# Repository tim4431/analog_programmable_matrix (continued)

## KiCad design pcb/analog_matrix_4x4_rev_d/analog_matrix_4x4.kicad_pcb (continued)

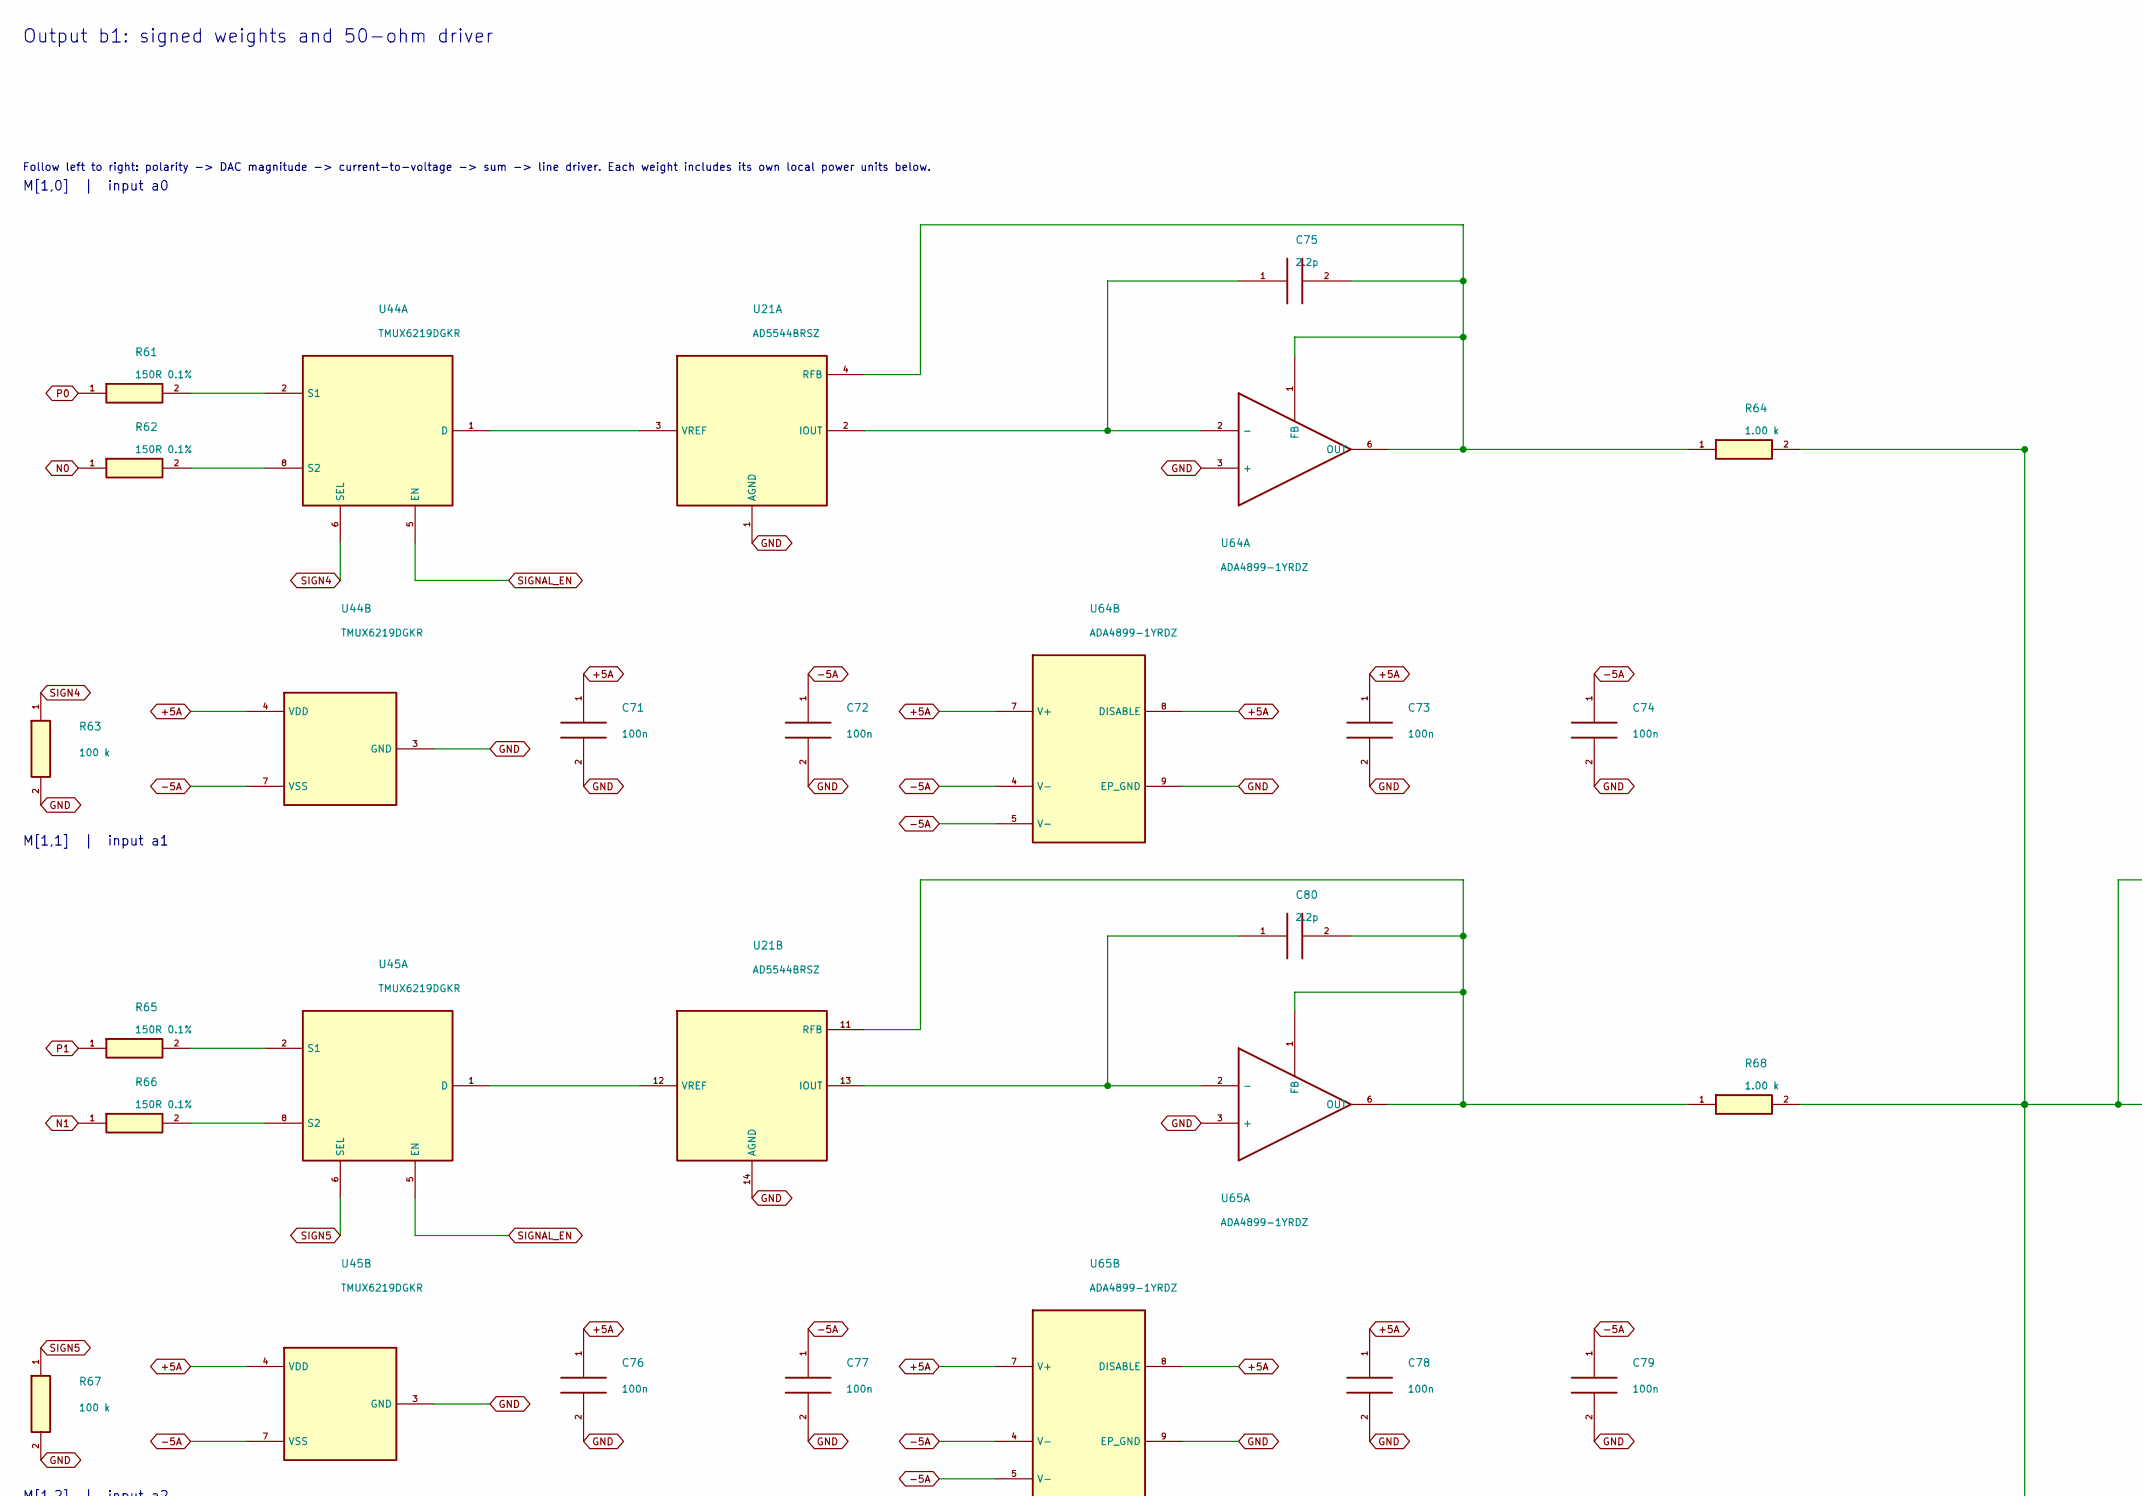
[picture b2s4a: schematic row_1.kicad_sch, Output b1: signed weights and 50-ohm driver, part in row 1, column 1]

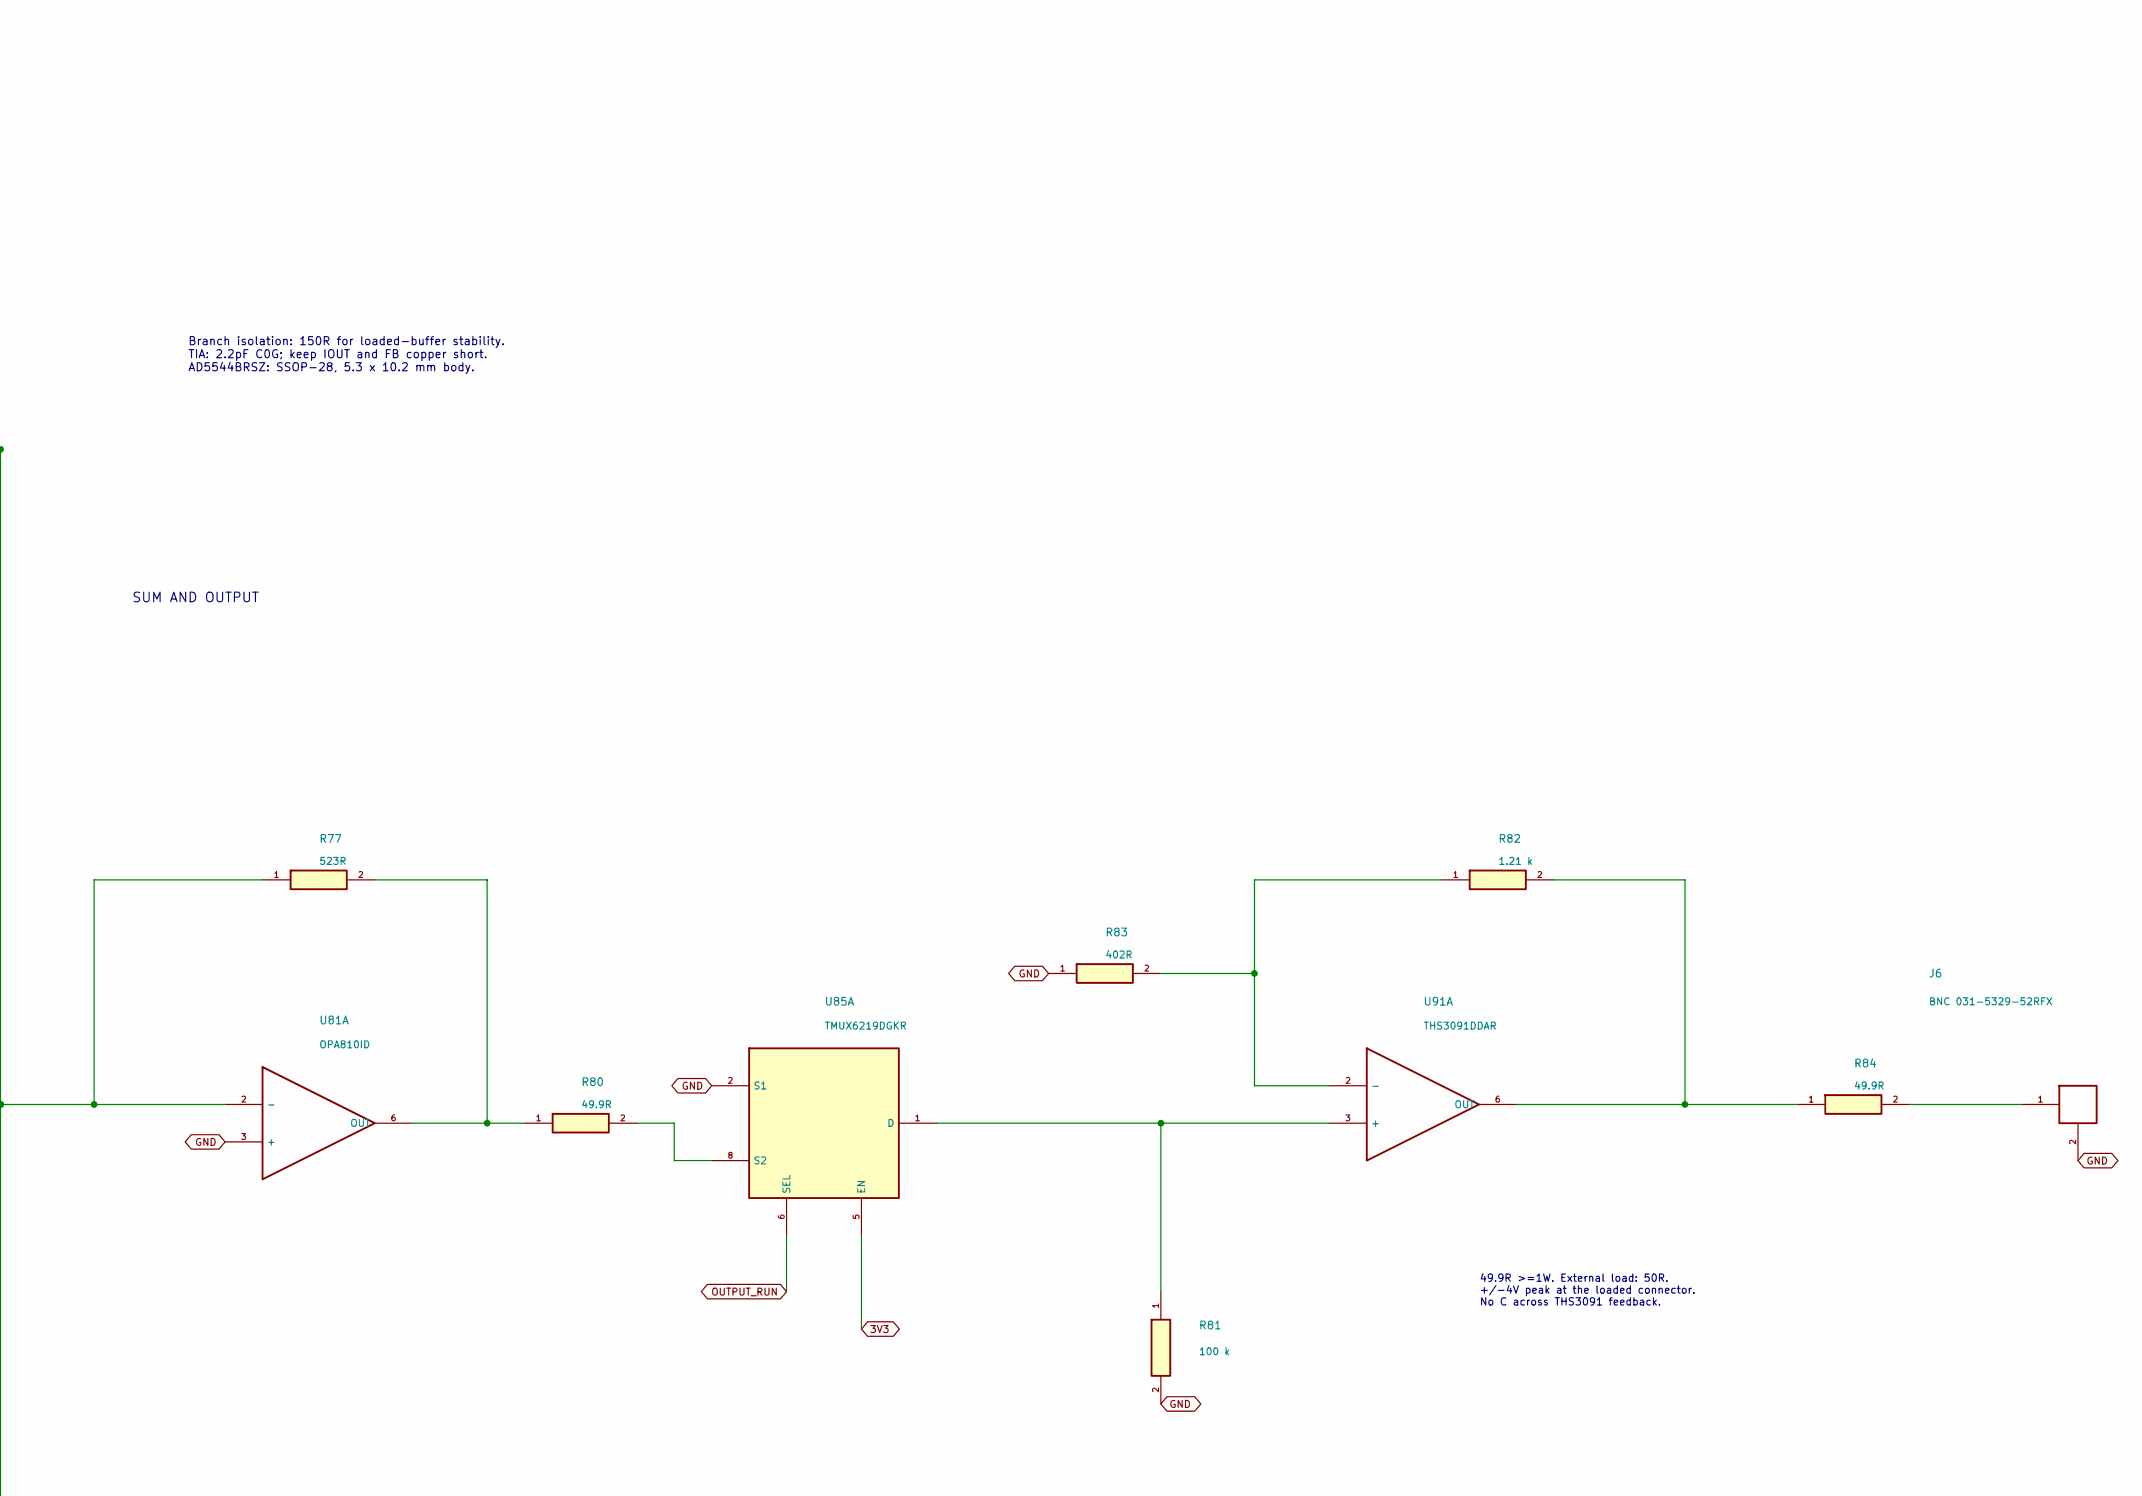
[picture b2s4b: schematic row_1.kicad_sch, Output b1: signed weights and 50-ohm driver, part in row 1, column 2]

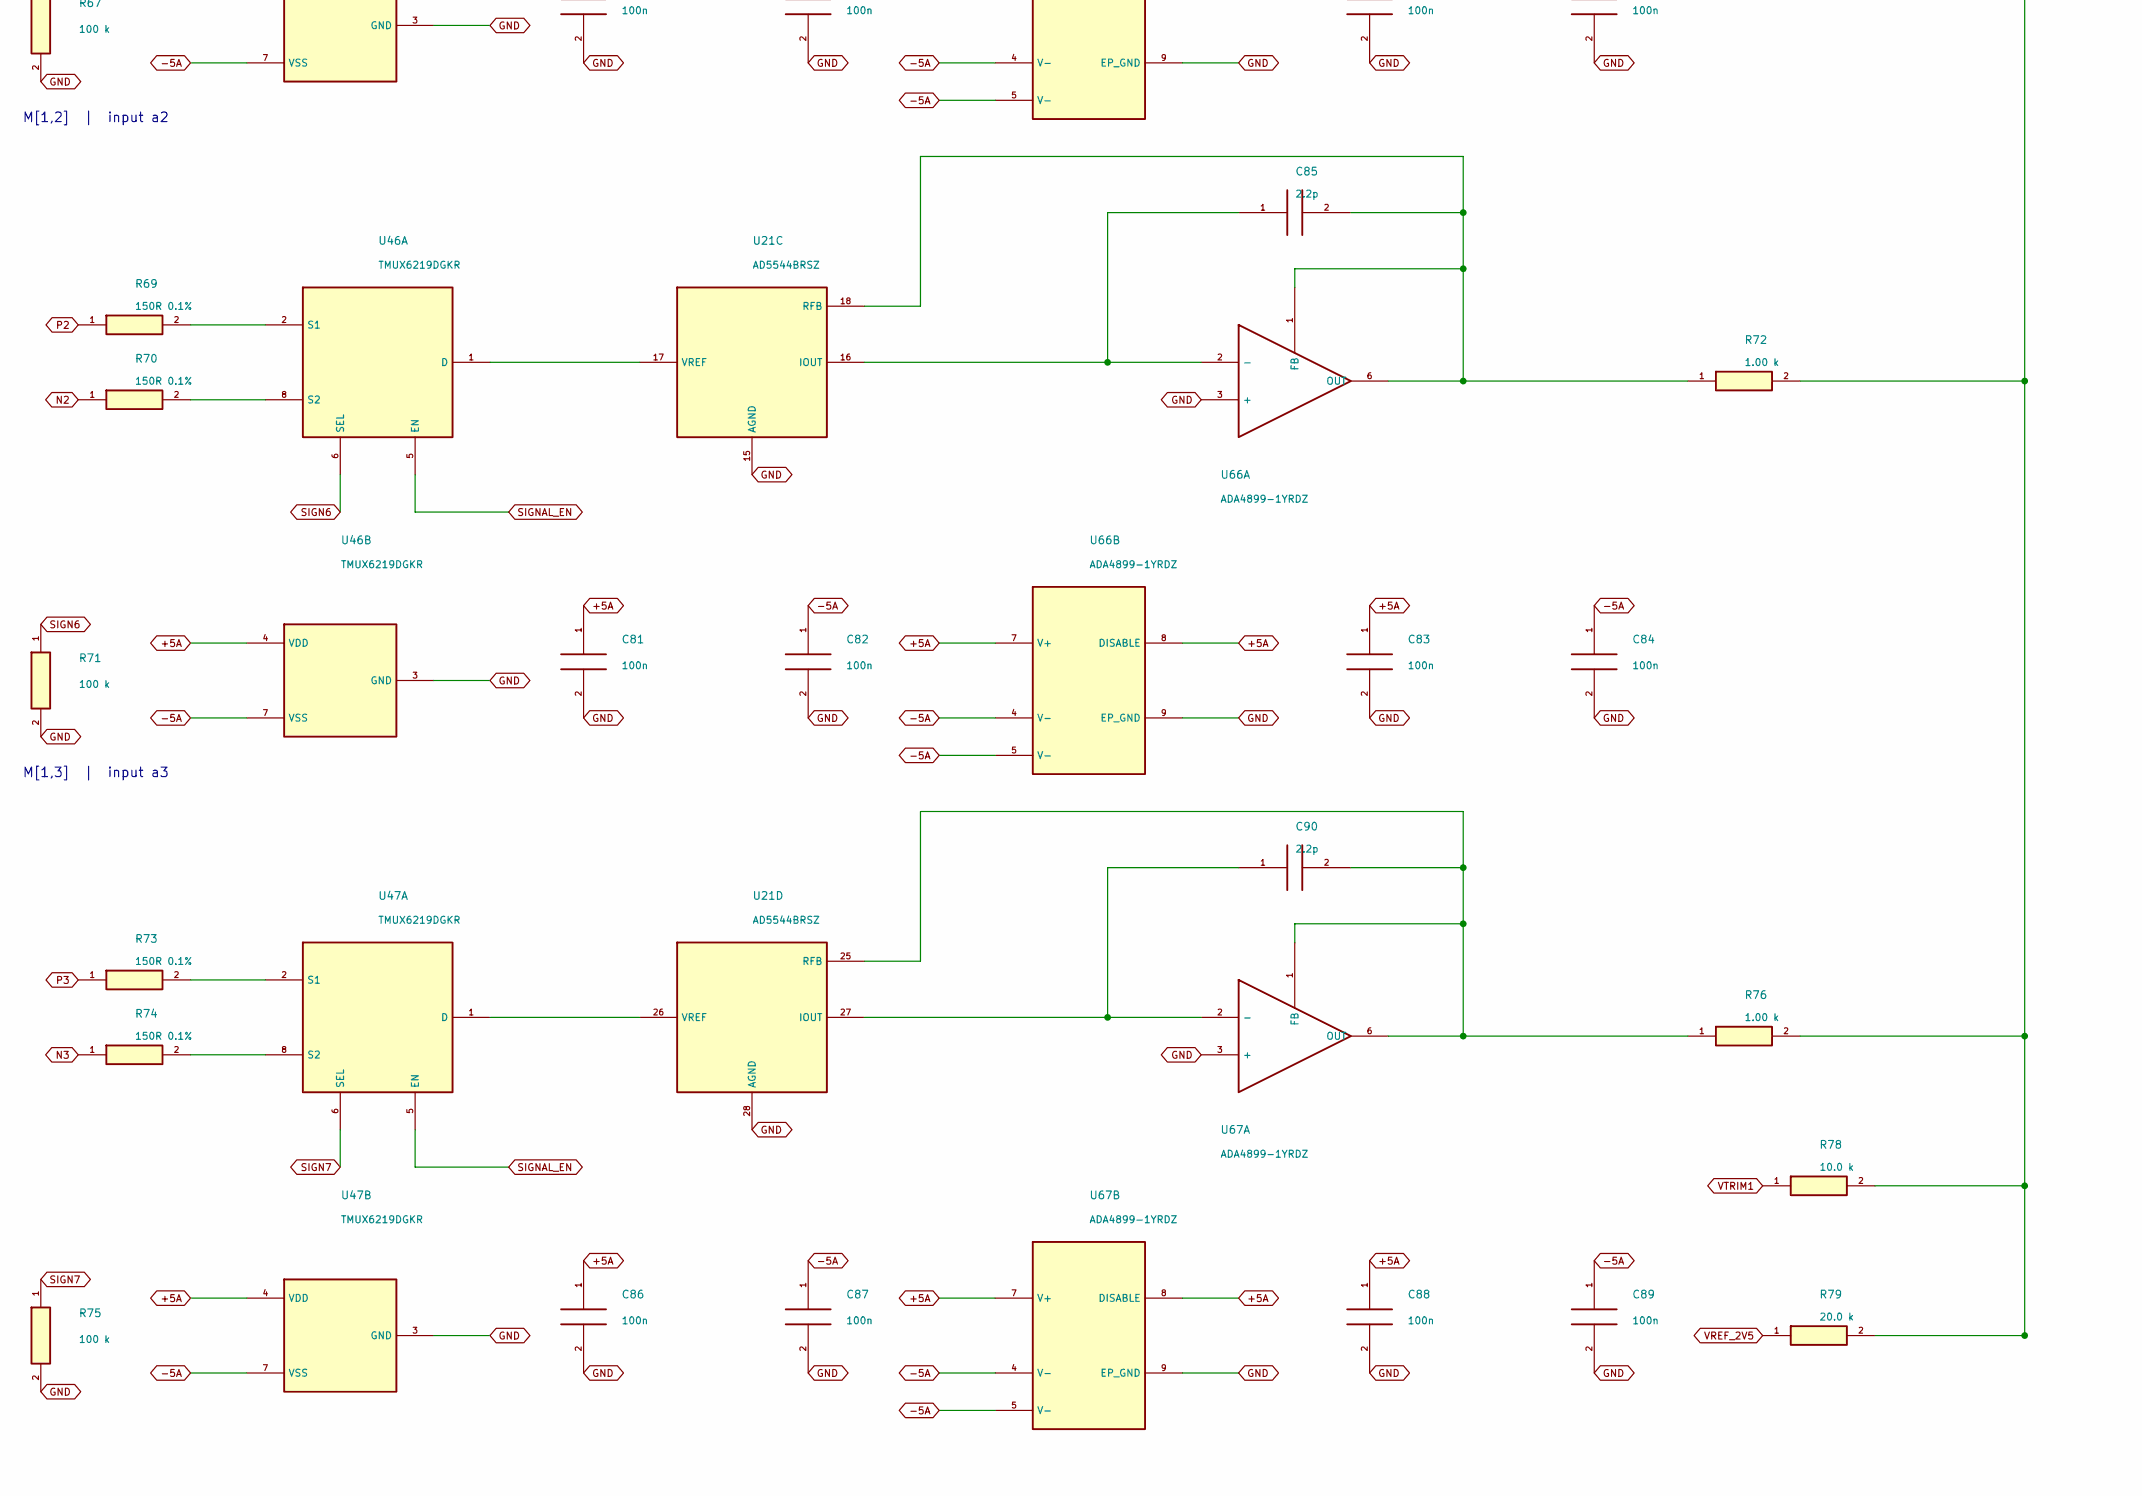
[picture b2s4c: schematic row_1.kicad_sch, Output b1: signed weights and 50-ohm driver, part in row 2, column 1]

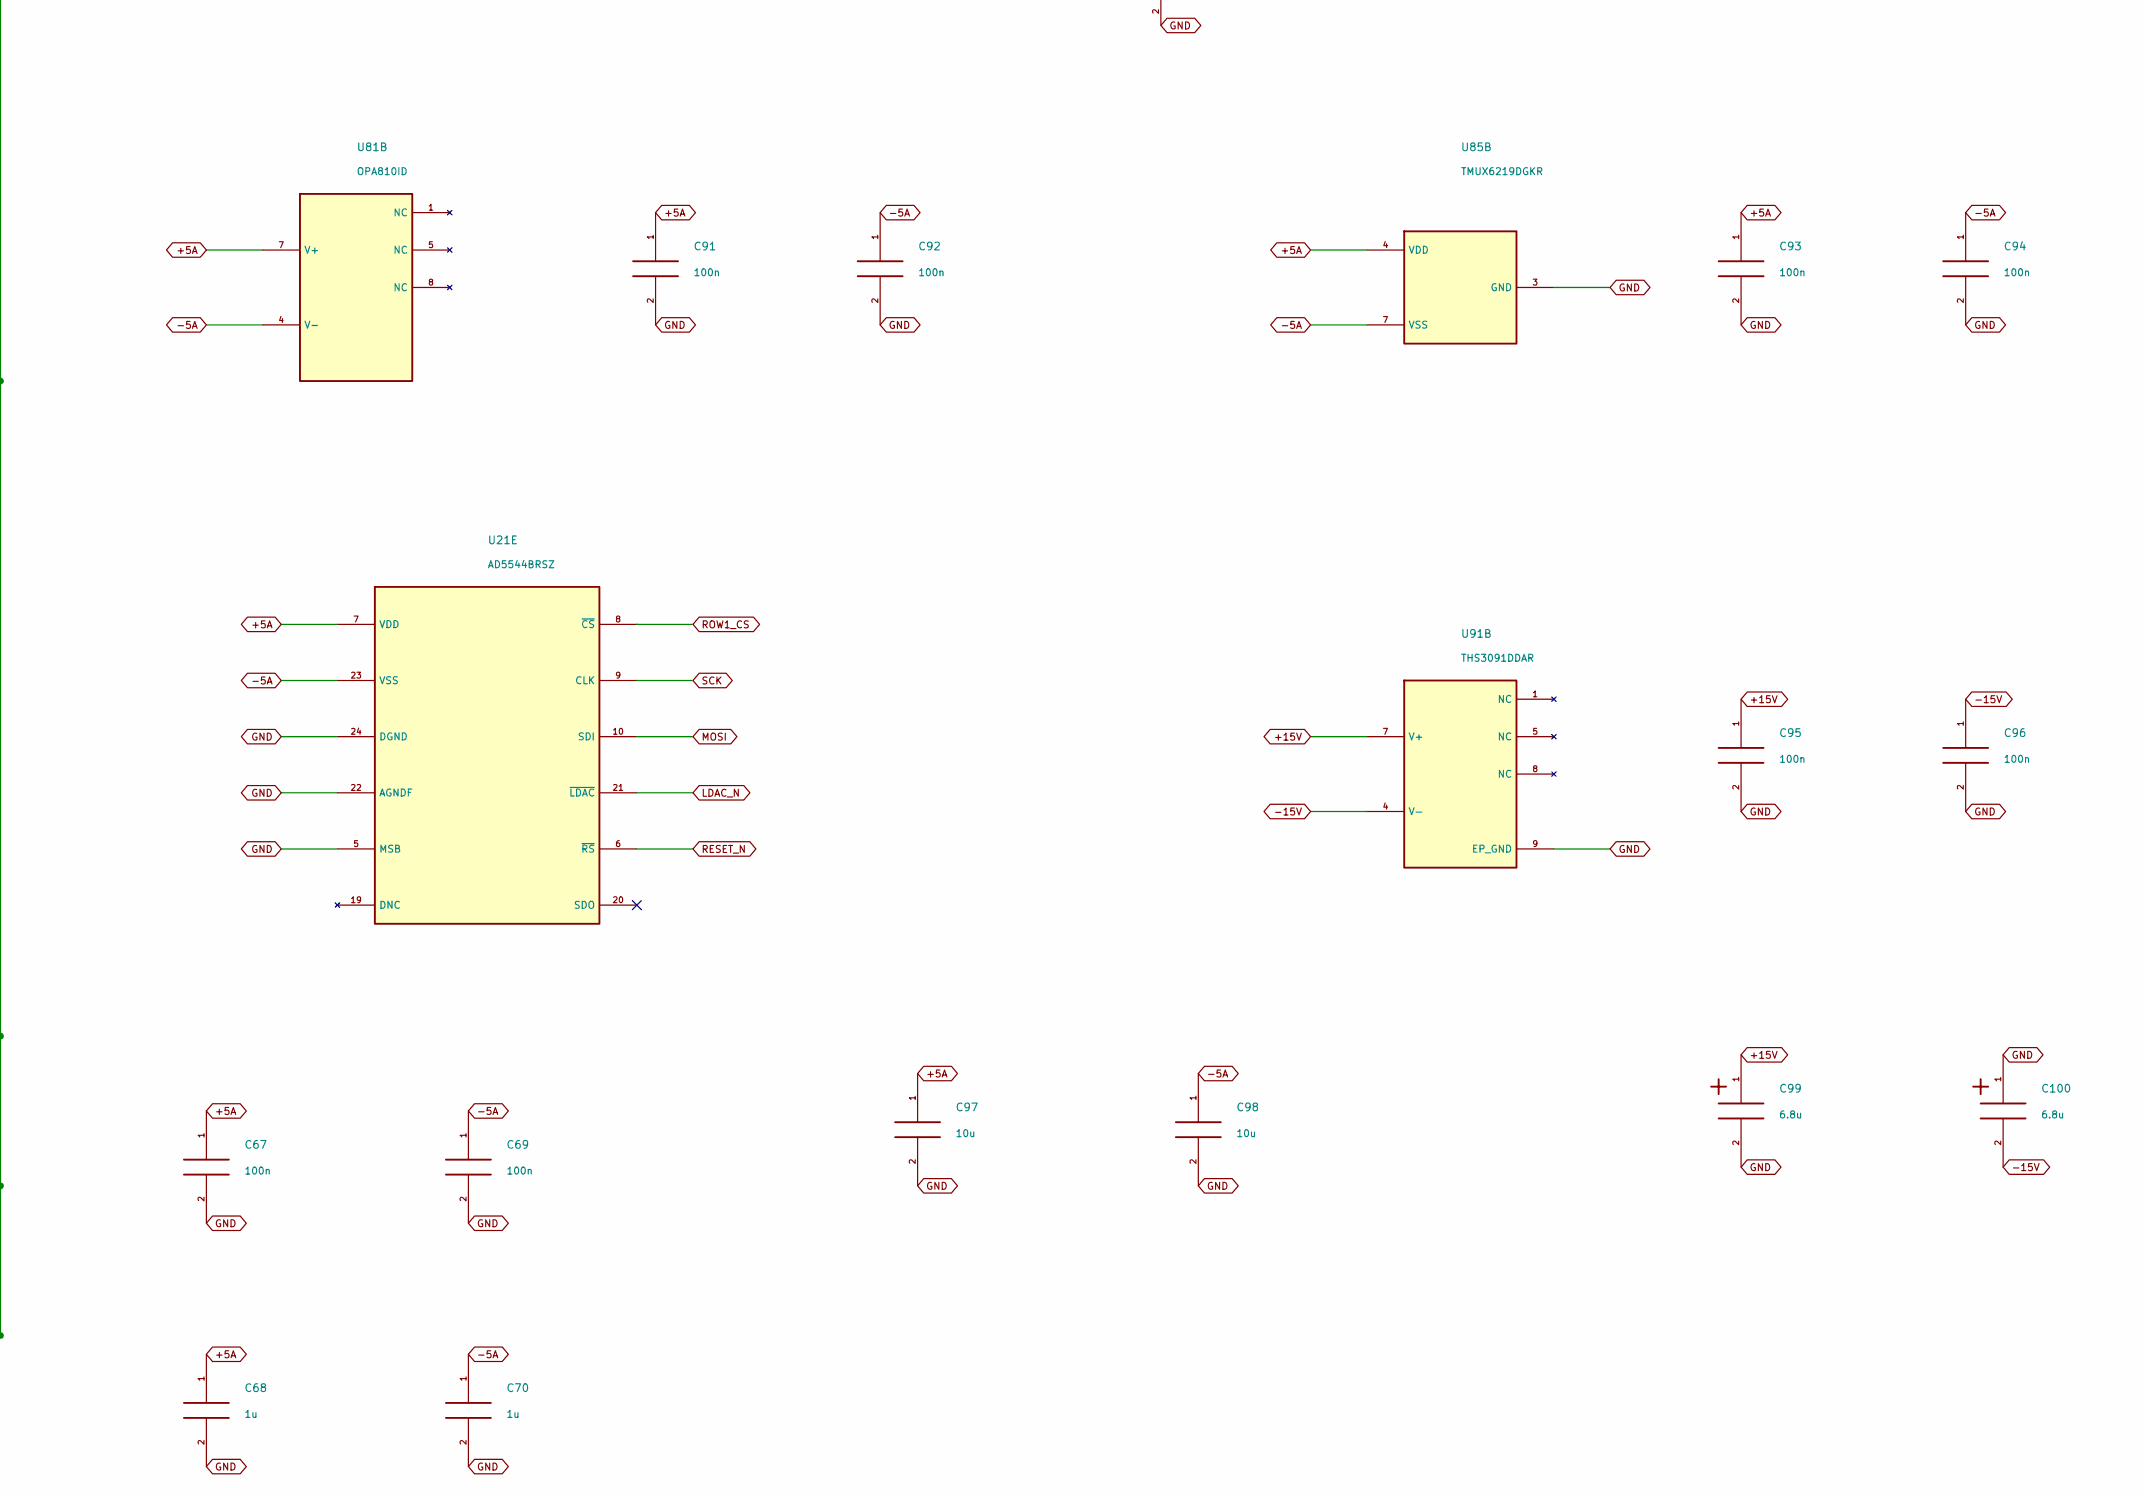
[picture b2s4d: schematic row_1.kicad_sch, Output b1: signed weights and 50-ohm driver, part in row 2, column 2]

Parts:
C67, C69, C71, C72, C73, C74, C76, C77, C78, C79, C81, C82, C83, C84, C86, C87, C88, C89, C91, C92, C93, C94, C95, C96: 100n; C_0603_1608Metric; Rating 25V X7R minimum; effective C after bias
C68, C70: 1u; C_0805_2012Metric; Rating 25V X7R minimum; effective C after bias
C75, C80, C85, C90: 2.2p; C_0402_1005Metric; Rating 50V C0G
C97, C98: 10u; C_0805_2012Metric; Rating 25V X7R minimum; effective C after bias
C99, C100: 6.8u; CP_EIA-3216-18_Kemet-A; Rating 25V polarized
J6: BNC 031-5329-52RFX; BNC_Amphenol_031-5329-52RFX_Vertical
R61, R62, R65, R66, R69, R70, R73, R74: 150R 0.1%; R_0603_1608Metric; Rating 0.1%, <=25ppm/C; 0.1W minimum
R63, R67, R71, R75, R81: 100 k; R_0603_1608Metric; Rating 0.1%, <=25ppm/C; 0.1W minimum
R64, R68, R72, R76: 1.00 k; R_0603_1608Metric; Rating 0.1%, <=25ppm/C; 0.1W minimum
R77: 523R; R_0603_1608Metric; Rating 0.1%, <=25ppm/C; 0.1W minimum
R78: 10.0 k; R_0603_1608Metric; Rating 0.1%, <=25ppm/C; 0.1W minimum
R79: 20.0 k; R_0603_1608Metric; Rating 0.1%, <=25ppm/C; 0.1W minimum
R80: 49.9R; R_0603_1608Metric; Rating 0.1%, <=25ppm/C; 0.1W minimum
R82: 1.21 k; R_0603_1608Metric; Rating 0.1%, <=25ppm/C; 0.1W minimum
R83: 402R; R_0603_1608Metric; Rating 0.1%, <=25ppm/C; 0.1W minimum
R84: 49.9R; R_2512_6332Metric; Rating 0.1%, <=25ppm/C; >=1W
U21: AD5544BRSZ; SSOP-28_5.3x10.2mm_P0.65mm
U44, U45, U46, U47, U85: TMUX6219DGKR; VSSOP-8_3x3mm_P0.65mm
U64, U65, U66, U67: ADA4899-1YRDZ; ADA4899_RD8_EP2.29x2.29
U81: OPA810ID; SOIC-8_3.9x4.9mm_P1.27mm
U91: THS3091DDAR; SOIC-8-1EP_3.9x4.9mm_P1.27mm_EP2.95x4.9mm_Mask2.71x3.4mm_Th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

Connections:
3V3: U85.5 (EN); also elsewhere on the board
+5A: C67.1, C68.1, C71.1, C73.1, C76.1, C78.1, C81.1, C83.1, C86.1, C88.1, C91.1, C93.1, C97.1, U21.7 (VDD), U44.4 (VDD), U45.4 (VDD), U46.4 (VDD), U47.4 (VDD), U64.7 (V+), U64.8 (DISABLE), U65.7 (V+), U65.8 (DISABLE), U66.7 (V+), U66.8 (DISABLE), U67.7 (V+), U67.8 (DISABLE), U81.7 (V+), U85.4 (VDD); also elsewhere on the board
+15V: C95.1, C99.1, U91.7 (V+); also elsewhere on the board
-5A: C69.1, C70.1, C72.1, C74.1, C77.1, C79.1, C82.1, C84.1, C87.1, C89.1, C92.1, C94.1, C98.1, U21.23 (VSS), U44.7 (VSS), U45.7 (VSS), U46.7 (VSS), U47.7 (VSS), U64.4 (V-), U64.5 (V-), U65.4 (V-), U65.5 (V-), U66.4 (V-), U66.5 (V-), U67.4 (V-), U67.5 (V-), U81.4 (V-), U85.7 (VSS); also elsewhere on the board
-15V: C96.1, C100.2, U91.4 (V-); also elsewhere on the board
GND: C67.2, C68.2, C69.2, C70.2, C71.2, C72.2, C73.2, C74.2, C76.2, C77.2, C78.2, C79.2, C81.2, C82.2, C83.2, C84.2, C86.2, C87.2, C88.2, C89.2, C91.2, C92.2, C93.2, C94.2, C95.2, C96.2, C97.2, C98.2, C99.2, C100.1, J6.2, R63.2, R67.2, R71.2, R75.2, R81.2, R83.1, U21.1 (AGND), U21.5 (MSB), U21.14 (AGND), U21.15 (AGND), U21.22 (AGNDF), U21.24 (DGND), U21.28 (AGND), U44.3 (GND), U45.3 (GND), U46.3 (GND), U47.3 (GND), U64.3 (+), U64.9 (EP_GND), U65.3 (+), U65.9 (EP_GND), U66.3 (+), U66.9 (EP_GND), U67.3 (+), U67.9 (EP_GND), U81.3 (+), U85.2 (S1), U85.3 (GND), U91.9 (EP_GND); also elsewhere on the board
LDAC_N: U21.21 (~LDAC); also elsewhere on the board
MOSI: U21.10 (SDI); also elsewhere on the board
N0: R62.1; also elsewhere on the board
N1: R66.1; also elsewhere on the board
N2: R70.1; also elsewhere on the board
N3: R74.1; also elsewhere on the board
unnamed: J6.1, R84.2
unnamed: C75.1, U21.2 (IOUT), U64.2 (-)
unnamed: C75.2, R64.1, U21.4 (RFB), U64.1 (FB), U64.6 (OUT)
unnamed: U21.3 (VREF), U44.1 (D)
unnamed: C80.1, U21.13 (IOUT), U65.2 (-)
unnamed: C80.2, R68.1, U21.11 (RFB), U65.1 (FB), U65.6 (OUT)
unnamed: U21.12 (VREF), U45.1 (D)
unnamed: C85.1, U21.16 (IOUT), U66.2 (-)
unnamed: C85.2, R72.1, U21.18 (RFB), U66.1 (FB), U66.6 (OUT)
unnamed: U21.17 (VREF), U46.1 (D)
unnamed: C90.1, U21.27 (IOUT), U67.2 (-)
unnamed: C90.2, R76.1, U21.25 (RFB), U67.1 (FB), U67.6 (OUT)
unnamed: U21.26 (VREF), U47.1 (D)
unnamed: R61.2, U44.2 (S1)
unnamed: R62.2, U44.8 (S2)
unnamed: R65.2, U45.2 (S1)
unnamed: R66.2, U45.8 (S2)
unnamed: R69.2, U46.2 (S1)
unnamed: R70.2, U46.8 (S2)
unnamed: R73.2, U47.2 (S1)
unnamed: R74.2, U47.8 (S2)
unnamed: R64.2, R68.2, R72.2, R76.2, R77.1, R78.2, R79.2, U81.2 (-)
unnamed: R77.2, R80.1, U81.6 (OUT)
unnamed: R81.1, U85.1 (D), U91.3 (+)
unnamed: R80.2, U85.8 (S2)
unnamed: R82.1, R83.2, U91.2 (-)
unnamed: R82.2, R84.1, U91.6 (OUT)
OUTPUT_RUN: U85.6 (SEL); also elsewhere on the board
P0: R61.1; also elsewhere on the board
P1: R65.1; also elsewhere on the board
P2: R69.1; also elsewhere on the board
P3: R73.1; also elsewhere on the board
RESET_N: U21.6 (~RS); also elsewhere on the board
ROW1_CS: U21.8 (~CS); also elsewhere on the board
SCK: U21.9 (CLK); also elsewhere on the board
SIGN4: R63.1, U44.6 (SEL); also elsewhere on the board
SIGN5: R67.1, U45.6 (SEL); also elsewhere on the board
SIGN6: R71.1, U46.6 (SEL); also elsewhere on the board
SIGN7: R75.1, U47.6 (SEL); also elsewhere on the board
SIGNAL_EN: U44.5 (EN), U45.5 (EN), U46.5 (EN), U47.5 (EN); also elsewhere on the board
VREF_2V5: R79.1; also elsewhere on the board
VTRIM1: R78.1; also elsewhere on the board

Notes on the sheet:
Output b1: signed weights and 50-ohm driver
Follow left to right: polarity -> DAC magnitude -> current-to-voltage -> sum -> line driver. Each weight includes its own local power units below.
M[1,0] | input a0
M[1,1] | input a1
M[1,2] | input a2
M[1,3] | input a3
SUM AND OUTPUT
49.9R >=1W. External load: 50R. +/-4V peak at the loaded connector. No C across THS3091 feedback.
Branch isolation: 150R for loaded-buffer stability. TIA: 2.2pF C0G; keep IOUT and FB copper short. AD5544BRSZ: SSOP-28, 5.3 x 10.2 mm body.

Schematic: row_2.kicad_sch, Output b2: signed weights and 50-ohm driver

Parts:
C101, C103, C105, C106, C107, C108, C110, C111, C112, C113, C115, C116, C117, C118, C120, C121, C122, C123, C125, C126, C127, C128, C129, C130: 100n; C_0603_1608Metric; Rating 25V X7R minimum; effective C after bias
C102, C104: 1u; C_0805_2012Metric; Rating 25V X7R minimum; effective C after bias
C109, C114, C119, C124: 2.2p; C_0402_1005Metric; Rating 50V C0G
C131, C132: 10u; C_0805_2012Metric; Rating 25V X7R minimum; effective C after bias
C133, C134: 6.8u; CP_EIA-3216-18_Kemet-A; Rating 25V polarized
J7: BNC 031-5329-52RFX; BNC_Amphenol_031-5329-52RFX_Vertical
R85, R86, R89, R90, R93, R94, R97, R98: 150R 0.1%; R_0603_1608Metric; Rating 0.1%, <=25ppm/C; 0.1W minimum
R87, R91, R95, R99, R105: 100 k; R_0603_1608Metric; Rating 0.1%, <=25ppm/C; 0.1W minimum
R88, R92, R96, R100: 1.00 k; R_0603_1608Metric; Rating 0.1%, <=25ppm/C; 0.1W minimum
R101: 523R; R_0603_1608Metric; Rating 0.1%, <=25ppm/C; 0.1W minimum
R102: 10.0 k; R_0603_1608Metric; Rating 0.1%, <=25ppm/C; 0.1W minimum
R103: 20.0 k; R_0603_1608Metric; Rating 0.1%, <=25ppm/C; 0.1W minimum
R104: 49.9R; R_0603_1608Metric; Rating 0.1%, <=25ppm/C; 0.1W minimum
R106: 1.21 k; R_0603_1608Metric; Rating 0.1%, <=25ppm/C; 0.1W minimum
R107: 402R; R_0603_1608Metric; Rating 0.1%, <=25ppm/C; 0.1W minimum
R108: 49.9R; R_2512_6332Metric; Rating 0.1%, <=25ppm/C; >=1W
U22: AD5544BRSZ; SSOP-28_5.3x10.2mm_P0.65mm
U48, U49, U50, U51, U86: TMUX6219DGKR; VSSOP-8_3x3mm_P0.65mm
U68, U69, U70, U71: ADA4899-1YRDZ; ADA4899_RD8_EP2.29x2.29
U82: OPA810ID; SOIC-8_3.9x4.9mm_P1.27mm
U92: THS3091DDAR; SOIC-8-1EP_3.9x4.9mm_P1.27mm_EP2.95x4.9mm_Mask2.71x3.4mm_Th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

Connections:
3V3: U86.5 (EN); also elsewhere on the board
+5A: C101.1, C102.1, C105.1, C107.1, C110.1, C112.1, C115.1, C117.1, C120.1, C122.1, C125.1, C127.1, C131.1, U22.7 (VDD), U48.4 (VDD), U49.4 (VDD), U50.4 (VDD), U51.4 (VDD), U68.7 (V+), U68.8 (DISABLE), U69.7 (V+), U69.8 (DISABLE), U70.7 (V+), U70.8 (DISABLE), U71.7 (V+), U71.8 (DISABLE), U82.7 (V+), U86.4 (VDD); also elsewhere on the board
+15V: C129.1, C133.1, U92.7 (V+); also elsewhere on the board
-5A: C103.1, C104.1, C106.1, C108.1, C111.1, C113.1, C116.1, C118.1, C121.1, C123.1, C126.1, C128.1, C132.1, U22.23 (VSS), U48.7 (VSS), U49.7 (VSS), U50.7 (VSS), U51.7 (VSS), U68.4 (V-), U68.5 (V-), U69.4 (V-), U69.5 (V-), U70.4 (V-), U70.5 (V-), U71.4 (V-), U71.5 (V-), U82.4 (V-), U86.7 (VSS); also elsewhere on the board
-15V: C130.1, C134.2, U92.4 (V-); also elsewhere on the board
GND: C101.2, C102.2, C103.2, C104.2, C105.2, C106.2, C107.2, C108.2, C110.2, C111.2, C112.2, C113.2, C115.2, C116.2, C117.2, C118.2, C120.2, C121.2, C122.2, C123.2, C125.2, C126.2, C127.2, C128.2, C129.2, C130.2, C131.2, C132.2, C133.2, C134.1, J7.2, R87.2, R91.2, R95.2, R99.2, R105.2, R107.1, U22.1 (AGND), U22.5 (MSB), U22.14 (AGND), U22.15 (AGND), U22.22 (AGNDF), U22.24 (DGND), U22.28 (AGND), U48.3 (GND), U49.3 (GND), U50.3 (GND), U51.3 (GND), U68.3 (+), U68.9 (EP_GND), U69.3 (+), U69.9 (EP_GND), U70.3 (+), U70.9 (EP_GND), U71.3 (+), U71.9 (EP_GND), U82.3 (+), U86.2 (S1), U86.3 (GND), U92.9 (EP_GND); also elsewhere on the board
LDAC_N: U22.21 (~LDAC); also elsewhere on the board
MOSI: U22.10 (SDI); also elsewhere on the board
N0: R86.1; also elsewhere on the board
N1: R90.1; also elsewhere on the board
N2: R94.1; also elsewhere on the board
N3: R98.1; also elsewhere on the board
unnamed: J7.1, R108.2
unnamed: C109.1, U22.2 (IOUT), U68.2 (-)
unnamed: C109.2, R88.1, U22.4 (RFB), U68.1 (FB), U68.6 (OUT)
unnamed: U22.3 (VREF), U48.1 (D)
unnamed: C114.1, U22.13 (IOUT), U69.2 (-)
unnamed: C114.2, R92.1, U22.11 (RFB), U69.1 (FB), U69.6 (OUT)
unnamed: U22.12 (VREF), U49.1 (D)
unnamed: C119.1, U22.16 (IOUT), U70.2 (-)
unnamed: C119.2, R96.1, U22.18 (RFB), U70.1 (FB), U70.6 (OUT)
unnamed: U22.17 (VREF), U50.1 (D)
unnamed: C124.1, U22.27 (IOUT), U71.2 (-)
unnamed: C124.2, R100.1, U22.25 (RFB), U71.1 (FB), U71.6 (OUT)
unnamed: U22.26 (VREF), U51.1 (D)
unnamed: R85.2, U48.2 (S1)
unnamed: R86.2, U48.8 (S2)
unnamed: R89.2, U49.2 (S1)
unnamed: R90.2, U49.8 (S2)
unnamed: R93.2, U50.2 (S1)
unnamed: R94.2, U50.8 (S2)
unnamed: R97.2, U51.2 (S1)
unnamed: R98.2, U51.8 (S2)
unnamed: R88.2, R92.2, R96.2, R100.2, R101.1, R102.2, R103.2, U82.2 (-)
unnamed: R101.2, R104.1, U82.6 (OUT)
unnamed: R105.1, U86.1 (D), U92.3 (+)
unnamed: R104.2, U86.8 (S2)
unnamed: R106.1, R107.2, U92.2 (-)
unnamed: R106.2, R108.1, U92.6 (OUT)
OUTPUT_RUN: U86.6 (SEL); also elsewhere on the board
P0: R85.1; also elsewhere on the board
P1: R89.1; also elsewhere on the board
P2: R93.1; also elsewhere on the board
P3: R97.1; also elsewhere on the board
RESET_N: U22.6 (~RS); also elsewhere on the board
ROW2_CS: U22.8 (~CS); also elsewhere on the board
SCK: U22.9 (CLK); also elsewhere on the board
SIGN8: R87.1, U48.6 (SEL); also elsewhere on the board
SIGN9: R91.1, U49.6 (SEL); also elsewhere on the board
SIGN10: R95.1, U50.6 (SEL); also elsewhere on the board
SIGN11: R99.1, U51.6 (SEL); also elsewhere on the board
SIGNAL_EN: U48.5 (EN), U49.5 (EN), U50.5 (EN), U51.5 (EN); also elsewhere on the board
VREF_2V5: R103.1; also elsewhere on the board
VTRIM2: R102.1; also elsewhere on the board

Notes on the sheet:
Output b2: signed weights and 50-ohm driver
Follow left to right: polarity -> DAC magnitude -> current-to-voltage -> sum -> line driver. Each weight includes its own local power units below.
M[2,0] | input a0
M[2,1] | input a1
M[2,2] | input a2
M[2,3] | input a3
SUM AND OUTPUT
49.9R >=1W. External load: 50R. +/-4V peak at the loaded connector. No C across THS3091 feedback.
Branch isolation: 150R for loaded-buffer stability. TIA: 2.2pF C0G; keep IOUT and FB copper short. AD5544BRSZ: SSOP-28, 5.3 x 10.2 mm body.

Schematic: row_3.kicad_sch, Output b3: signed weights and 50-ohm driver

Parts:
C135, C137, C139, C140, C141, C142, C144, C145, C146, C147, C149, C150, C151, C152, C154, C155, C156, C157, C159, C160, C161, C162, C163, C164: 100n; C_0603_1608Metric; Rating 25V X7R minimum; effective C after bias
C136, C138: 1u; C_0805_2012Metric; Rating 25V X7R minimum; effective C after bias
C143, C148, C153, C158: 2.2p; C_0402_1005Metric; Rating 50V C0G
C165, C166: 10u; C_0805_2012Metric; Rating 25V X7R minimum; effective C after bias
C167, C168: 6.8u; CP_EIA-3216-18_Kemet-A; Rating 25V polarized
J8: BNC 031-5329-52RFX; BNC_Amphenol_031-5329-52RFX_Vertical
R109, R110, R113, R114, R117, R118, R121, R122: 150R 0.1%; R_0603_1608Metric; Rating 0.1%, <=25ppm/C; 0.1W minimum
R111, R115, R119, R123, R129: 100 k; R_0603_1608Metric; Rating 0.1%, <=25ppm/C; 0.1W minimum
R112, R116, R120, R124: 1.00 k; R_0603_1608Metric; Rating 0.1%, <=25ppm/C; 0.1W minimum
R125: 523R; R_0603_1608Metric; Rating 0.1%, <=25ppm/C; 0.1W minimum
R126: 10.0 k; R_0603_1608Metric; Rating 0.1%, <=25ppm/C; 0.1W minimum
R127: 20.0 k; R_0603_1608Metric; Rating 0.1%, <=25ppm/C; 0.1W minimum
R128: 49.9R; R_0603_1608Metric; Rating 0.1%, <=25ppm/C; 0.1W minimum
R130: 1.21 k; R_0603_1608Metric; Rating 0.1%, <=25ppm/C; 0.1W minimum
R131: 402R; R_0603_1608Metric; Rating 0.1%, <=25ppm/C; 0.1W minimum
R132: 49.9R; R_2512_6332Metric; Rating 0.1%, <=25ppm/C; >=1W
U23: AD5544BRSZ; SSOP-28_5.3x10.2mm_P0.65mm
U52, U53, U54, U55, U87: TMUX6219DGKR; VSSOP-8_3x3mm_P0.65mm
U72, U73, U74, U75: ADA4899-1YRDZ; ADA4899_RD8_EP2.29x2.29
U83: OPA810ID; SOIC-8_3.9x4.9mm_P1.27mm
U93: THS3091DDAR; SOIC-8-1EP_3.9x4.9mm_P1.27mm_EP2.95x4.9mm_Mask2.71x3.4mm_Th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

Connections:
3V3: U87.5 (EN); also elsewhere on the board
+5A: C135.1, C136.1, C139.1, C141.1, C144.1, C146.1, C149.1, C151.1, C154.1, C156.1, C159.1, C161.1, C165.1, U23.7 (VDD), U52.4 (VDD), U53.4 (VDD), U54.4 (VDD), U55.4 (VDD), U72.7 (V+), U72.8 (DISABLE), U73.7 (V+), U73.8 (DISABLE), U74.7 (V+), U74.8 (DISABLE), U75.7 (V+), U75.8 (DISABLE), U83.7 (V+), U87.4 (VDD); also elsewhere on the board
+15V: C163.1, C167.1, U93.7 (V+); also elsewhere on the board
-5A: C137.1, C138.1, C140.1, C142.1, C145.1, C147.1, C150.1, C152.1, C155.1, C157.1, C160.1, C162.1, C166.1, U23.23 (VSS), U52.7 (VSS), U53.7 (VSS), U54.7 (VSS), U55.7 (VSS), U72.4 (V-), U72.5 (V-), U73.4 (V-), U73.5 (V-), U74.4 (V-), U74.5 (V-), U75.4 (V-), U75.5 (V-), U83.4 (V-), U87.7 (VSS); also elsewhere on the board
-15V: C164.1, C168.2, U93.4 (V-); also elsewhere on the board
GND: C135.2, C136.2, C137.2, C138.2, C139.2, C140.2, C141.2, C142.2, C144.2, C145.2, C146.2, C147.2, C149.2, C150.2, C151.2, C152.2, C154.2, C155.2, C156.2, C157.2, C159.2, C160.2, C161.2, C162.2, C163.2, C164.2, C165.2, C166.2, C167.2, C168.1, J8.2, R111.2, R115.2, R119.2, R123.2, R129.2, R131.1, U23.1 (AGND), U23.5 (MSB), U23.14 (AGND), U23.15 (AGND), U23.22 (AGNDF), U23.24 (DGND), U23.28 (AGND), U52.3 (GND), U53.3 (GND), U54.3 (GND), U55.3 (GND), U72.3 (+), U72.9 (EP_GND), U73.3 (+), U73.9 (EP_GND), U74.3 (+), U74.9 (EP_GND), U75.3 (+), U75.9 (EP_GND), U83.3 (+), U87.2 (S1), U87.3 (GND), U93.9 (EP_GND); also elsewhere on the board
LDAC_N: U23.21 (~LDAC); also elsewhere on the board
MOSI: U23.10 (SDI); also elsewhere on the board
N0: R110.1; also elsewhere on the board
N1: R114.1; also elsewhere on the board
N2: R118.1; also elsewhere on the board
N3: R122.1; also elsewhere on the board
unnamed: J8.1, R132.2
unnamed: C143.1, U23.2 (IOUT), U72.2 (-)
unnamed: C143.2, R112.1, U23.4 (RFB), U72.1 (FB), U72.6 (OUT)
unnamed: U23.3 (VREF), U52.1 (D)
unnamed: C148.1, U23.13 (IOUT), U73.2 (-)
unnamed: C148.2, R116.1, U23.11 (RFB), U73.1 (FB), U73.6 (OUT)
unnamed: U23.12 (VREF), U53.1 (D)
unnamed: C153.1, U23.16 (IOUT), U74.2 (-)
unnamed: C153.2, R120.1, U23.18 (RFB), U74.1 (FB), U74.6 (OUT)
unnamed: U23.17 (VREF), U54.1 (D)
unnamed: C158.1, U23.27 (IOUT), U75.2 (-)
unnamed: C158.2, R124.1, U23.25 (RFB), U75.1 (FB), U75.6 (OUT)
unnamed: U23.26 (VREF), U55.1 (D)
unnamed: R109.2, U52.2 (S1)
unnamed: R110.2, U52.8 (S2)
unnamed: R113.2, U53.2 (S1)
unnamed: R114.2, U53.8 (S2)
unnamed: R117.2, U54.2 (S1)
unnamed: R118.2, U54.8 (S2)
unnamed: R121.2, U55.2 (S1)
unnamed: R122.2, U55.8 (S2)
unnamed: R112.2, R116.2, R120.2, R124.2, R125.1, R126.2, R127.2, U83.2 (-)
unnamed: R125.2, R128.1, U83.6 (OUT)
unnamed: R129.1, U87.1 (D), U93.3 (+)
unnamed: R128.2, U87.8 (S2)
unnamed: R130.1, R131.2, U93.2 (-)
unnamed: R130.2, R132.1, U93.6 (OUT)
OUTPUT_RUN: U87.6 (SEL); also elsewhere on the board
P0: R109.1; also elsewhere on the board
P1: R113.1; also elsewhere on the board
P2: R117.1; also elsewhere on the board
P3: R121.1; also elsewhere on the board
RESET_N: U23.6 (~RS); also elsewhere on the board
ROW3_CS: U23.8 (~CS); also elsewhere on the board
SCK: U23.9 (CLK); also elsewhere on the board
SIGN12: R111.1, U52.6 (SEL); also elsewhere on the board
SIGN13: R115.1, U53.6 (SEL); also elsewhere on the board
SIGN14: R119.1, U54.6 (SEL); also elsewhere on the board
SIGN15: R123.1, U55.6 (SEL); also elsewhere on the board
SIGNAL_EN: U52.5 (EN), U53.5 (EN), U54.5 (EN), U55.5 (EN); also elsewhere on the board
VREF_2V5: R127.1; also elsewhere on the board
VTRIM3: R126.1; also elsewhere on the board

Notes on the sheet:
Output b3: signed weights and 50-ohm driver
Follow left to right: polarity -> DAC magnitude -> current-to-voltage -> sum -> line driver. Each weight includes its own local power units below.
M[3,0] | input a0
M[3,1] | input a1
M[3,2] | input a2
M[3,3] | input a3
SUM AND OUTPUT
49.9R >=1W. External load: 50R. +/-4V peak at the loaded connector. No C across THS3091 feedback.
Branch isolation: 150R for loaded-buffer stability. TIA: 2.2pF C0G; keep IOUT and FB copper short. AD5544BRSZ: SSOP-28, 5.3 x 10.2 mm body.
